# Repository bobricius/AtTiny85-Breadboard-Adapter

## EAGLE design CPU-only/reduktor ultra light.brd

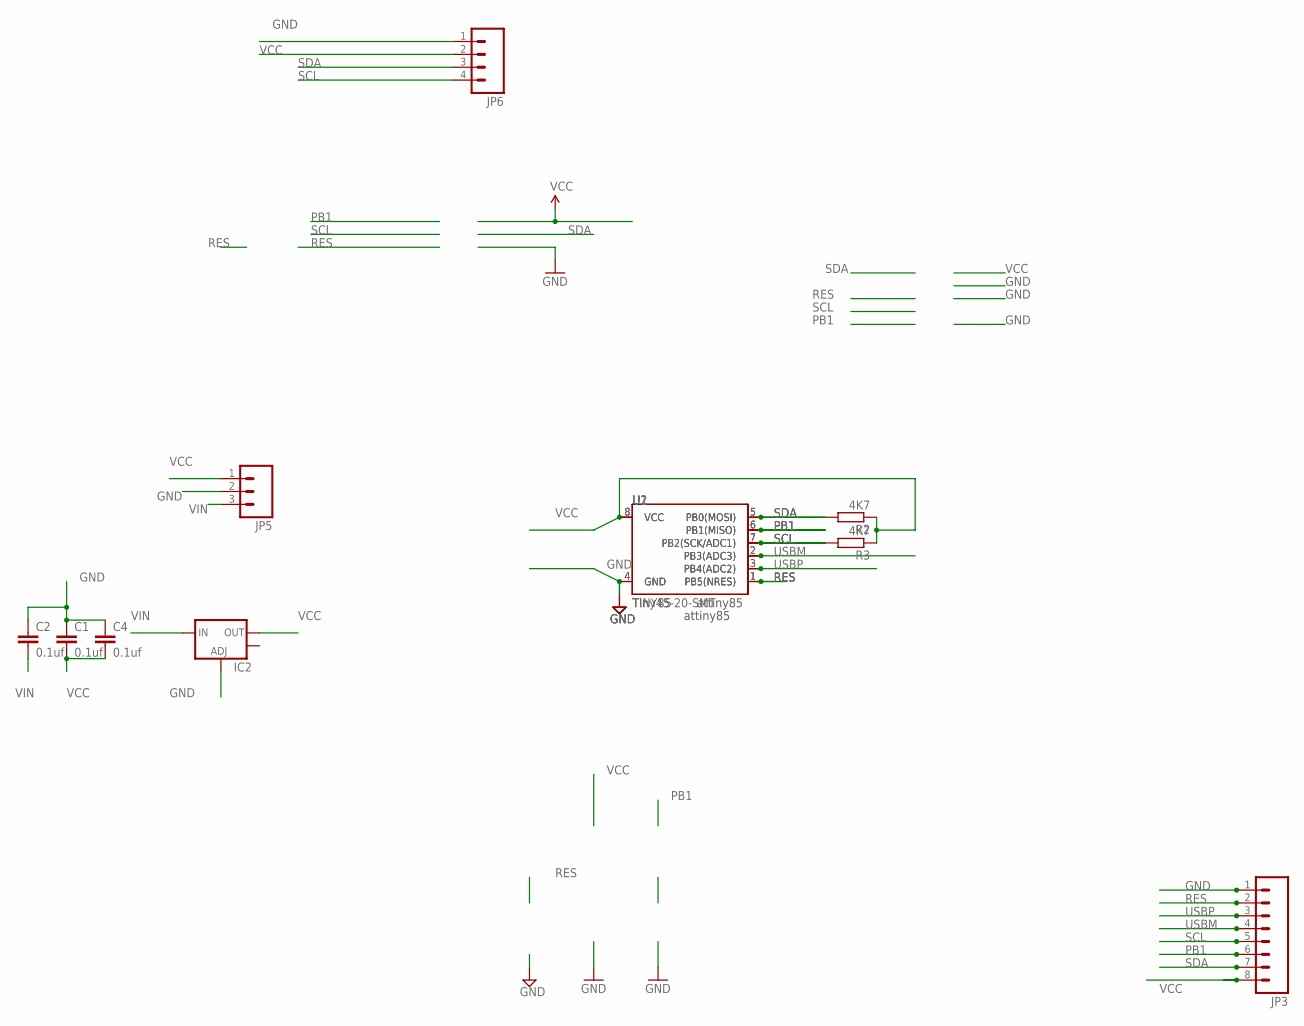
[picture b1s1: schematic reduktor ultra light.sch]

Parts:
C1, C2, C4: 0.1uf; 0603-CAP
IC2: V_REG_LM1117SOT223; SOT223
JP3: M08LOCK; 1X08_LOCK
JP5: M03LOCK; 1X03_LOCK
JP6: M04PTH; 1X04
R2, R3: 4K7; R0603
U1: TINY85; DIP08
U2: Tiny45-20-SMT; SO08-EIAJ

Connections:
GND: C1.1, C2.1, C4.1, IC2.1 (ADJ), JP3.1, JP5.2, JP6.1, U1.4 (GND), U2.4 (GND)
PB1: JP3.6, U1.6 (PB1(MISO)), U2.6 (PB1(MISO))
RES: JP3.2, U1.1 (PB5(NRES)), U2.1 (PB5(NRES))
SCL: JP3.5, JP6.4, R3.2, U1.7 (PB2(SCK/ADC1)), U2.7 (PB2(SCK/ADC1))
SDA: JP3.7, JP6.3, R2.2, U1.5 (PB0(MOSI)), U2.5 (PB0(MOSI))
USBM: JP3.4, U1.2 (PB3(ADC3)), U2.2 (PB3(ADC3))
USBP: JP3.3, U1.3 (PB4(ADC2)), U2.3 (PB4(ADC2))
VCC: C1.2, C4.2, IC2.2 (OUT), JP3.8, JP5.1, JP6.2, R2.1, R3.1, U1.8 (VCC), U2.8 (VCC)
VIN: C2.2, IC2.3 (IN), JP5.3

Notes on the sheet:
attiny85

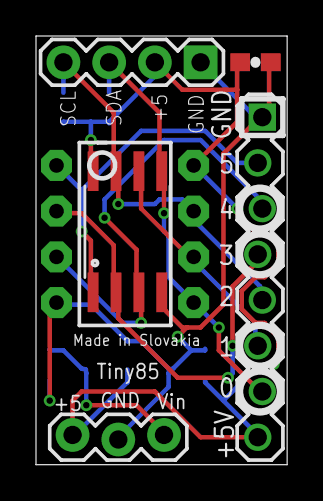
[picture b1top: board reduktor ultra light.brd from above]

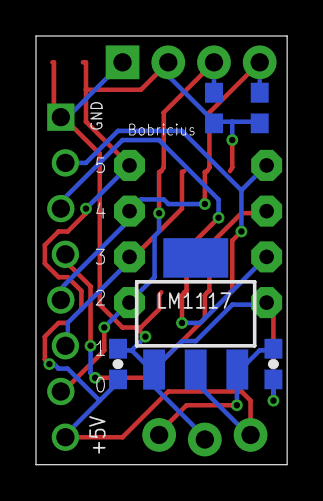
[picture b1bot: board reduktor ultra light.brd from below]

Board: 2 copper layers, 14.0 x 23.8 mm, 11 parts (5 on the bottom side), 9 nets.

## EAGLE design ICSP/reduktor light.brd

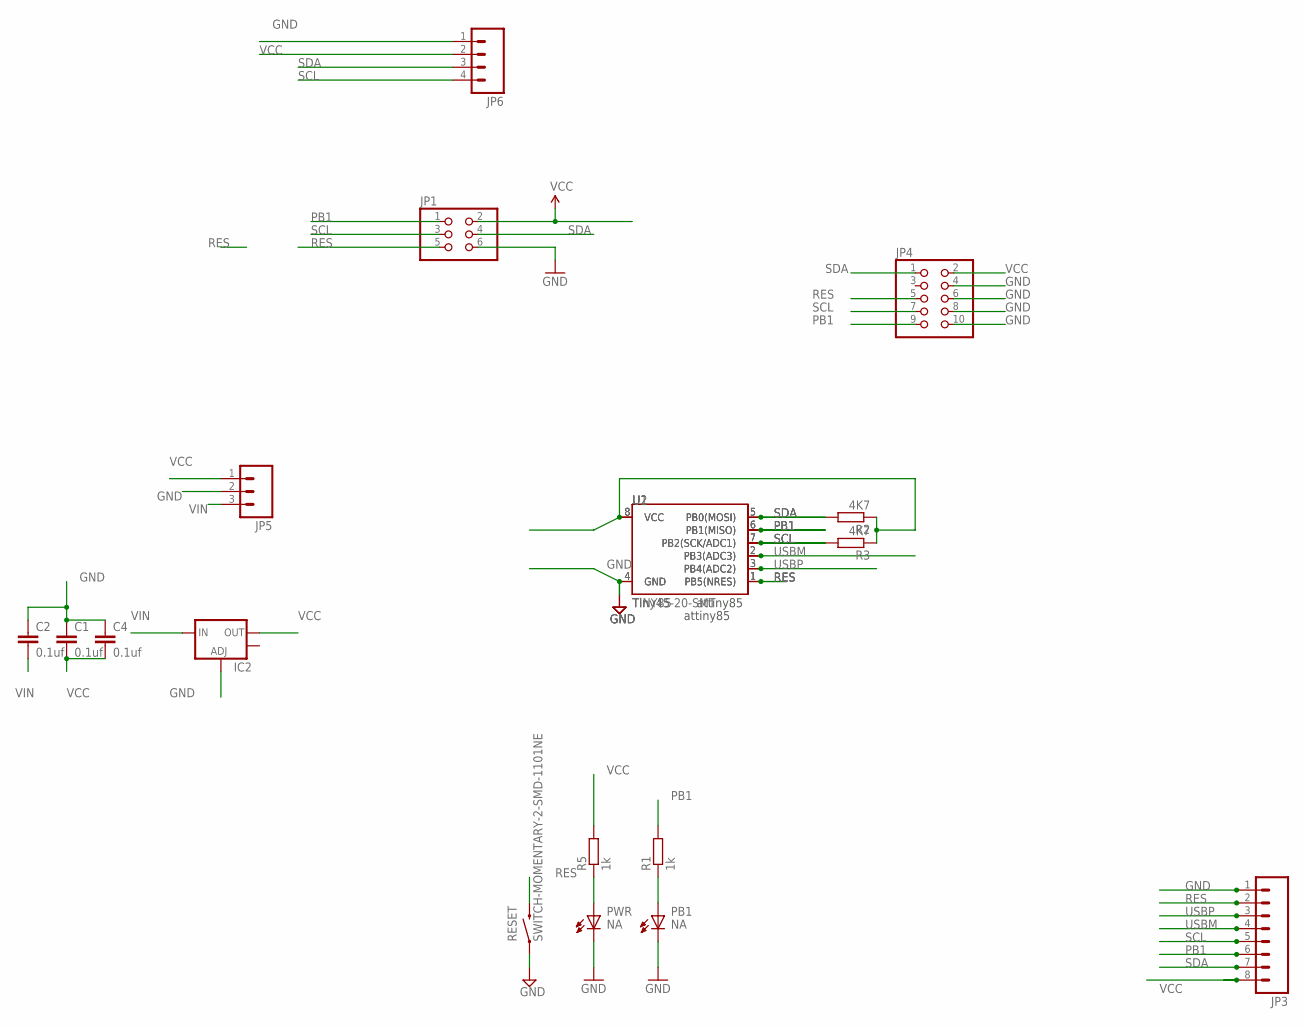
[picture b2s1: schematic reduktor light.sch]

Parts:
C1, C2, C4: 0.1uf; 0603-CAP
IC2: V_REG_LM1117SOT223; SOT223
JP1: PINHD-2X3; 2X03
JP3: M08LOCK_LONGPADS; 1X08_LOCK_LONGPADS
JP4: PINHD-2X5; 2X05
JP5: M03LONGPADS; 1X03_LONGPADS
JP6: M04PTH; 1X04
PB1: NA; LED-0603
PWR: NA; LED-0603
R1, R5: 1k; R0603
R2, R3: 4K7; R0603
RESET: SWITCH-MOMENTARY-2-SMD-1101NE; TACTILE-SWITCH-1101NE
U1: TINY85; DIP08
U2: Tiny45-20-SMT; SO08-EIAJ

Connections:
GND: C1.1, C2.1, C4.1, IC2.1 (ADJ), JP1.6, JP3.1, JP4.4, JP4.6, JP4.8, JP4.10, JP5.2, JP6.1, PB1.C, PWR.C, RESET.P$1 (1), U1.4 (GND), U2.4 (GND)
unnamed: PWR.A, R5.1
PB1: JP1.1, JP3.6, JP4.9, R1.2, U1.6 (PB1(MISO)), U2.6 (PB1(MISO))
PIN1R: PB1.A, R1.1
RES: JP1.5, JP3.2, JP4.5, RESET.P$2 (2), U1.1 (PB5(NRES)), U2.1 (PB5(NRES))
SCL: JP1.3, JP3.5, JP4.7, JP6.4, R3.2, U1.7 (PB2(SCK/ADC1)), U2.7 (PB2(SCK/ADC1))
SDA: JP1.4, JP3.7, JP4.1, JP6.3, R2.2, U1.5 (PB0(MOSI)), U2.5 (PB0(MOSI))
USBM: JP3.4, U1.2 (PB3(ADC3)), U2.2 (PB3(ADC3))
USBP: JP3.3, U1.3 (PB4(ADC2)), U2.3 (PB4(ADC2))
VCC: C1.2, C4.2, IC2.2 (OUT), JP1.2, JP3.8, JP4.2, JP5.1, JP6.2, R2.1, R3.1, R5.2, U1.8 (VCC), U2.8 (VCC)
VIN: C2.2, IC2.3 (IN), JP5.3

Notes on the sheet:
attiny85

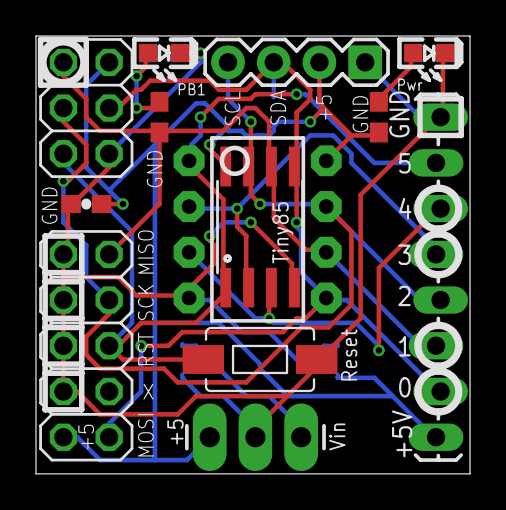
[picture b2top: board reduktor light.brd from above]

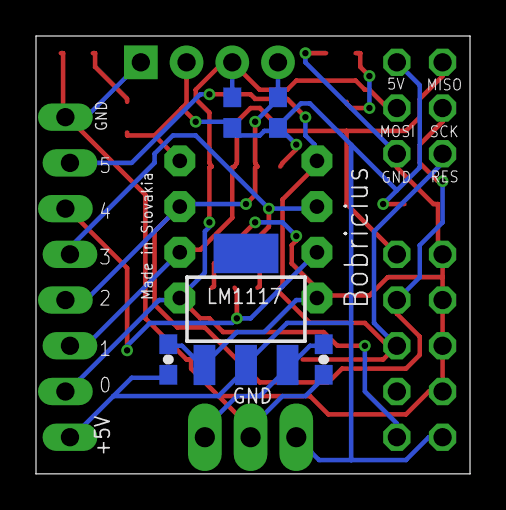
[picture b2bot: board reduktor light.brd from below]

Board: 2 copper layers, 24.1 x 24.3 mm, 18 parts (5 on the bottom side), 11 nets.

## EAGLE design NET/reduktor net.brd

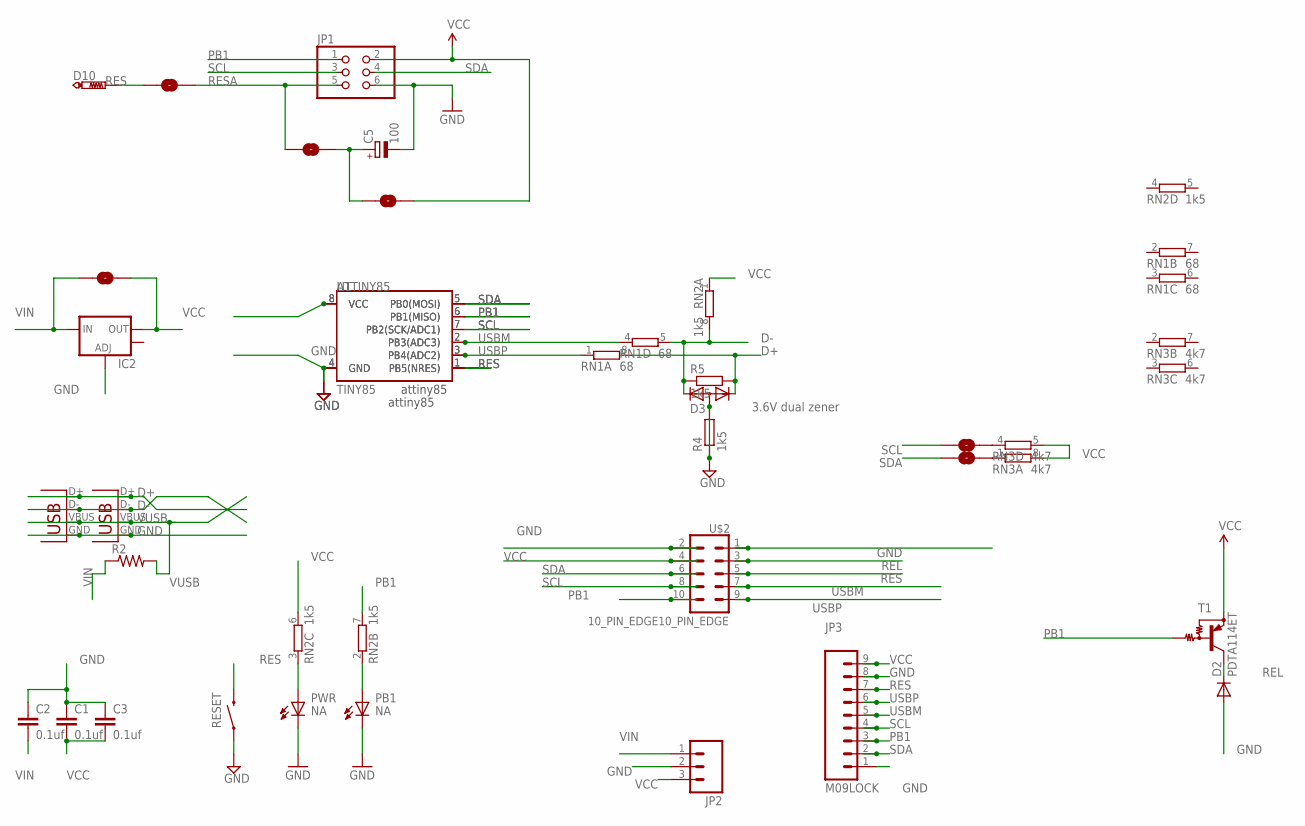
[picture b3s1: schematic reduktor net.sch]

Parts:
ATTINY85: ATTINY45; SO08-EIAJ
C1, C2, C3: 0.1uf; 0603-CAP
C5: 100; 153CLV-0405
D2: DIODESOD; SOD-323
D3: 3.6V dual zener; SOT23
D10: PTR1TP14SQ; TP14SQ
FUSE1, FUSE2, FUSE3, FUSE4, FUSE5, FUSE6: SOLDERJUMPERNO; SJ_2S-NO
IC2: V_REG_LM1117SOT223; SOT223
JP1: PINHD-2X3; 2X03
JP2: M03LOCK; 1X03_LOCK
JP3: M09LOCK; 1X09_LOCK
PB1: NA; LED-0603
PWR: NA; LED-0603
R2: RESISTOR0603-RES; 0603-RES
R4, R5: 1k5; R0603
RESET: SWITCH-MOMENTARY-2-SMD-1101NE; TACTILE-SWITCH-1101NE
RN1: 68; 0603-ARC
RN2: 1k5; 0603-ARC
RN3: 4k7; 0603-ARC
T1: PDTA114ET; ES_SOT23-3
U1: TINY85; DIP08
U$2: 10_PIN_EDGE10_PIN_EDGE; 10_PIN_EDGE
X5: USBSMD; USB-MINIB
X6: USB-MICROB

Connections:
D+: D3.1 (K1), R5.2, RN1.8 (2), X5.D+, X6.D+
D-: D3.2 (K2), R5.1, RN1.5 (2), RN2.8 (2), X5.D-, X6.D-
GND: ATTINY85.4 (GND), C1.1, C2.1, C3.1, C5.-, D2.2 (A), D3.3 (A), IC2.1 (ADJ), JP1.6, JP2.2, JP3.1, JP3.8, PB1.C, PWR.C, R4.1, R4.2, RESET.P$1 (1), U1.4 (GND), U$2.1, U$2.2, X5.GND, X6.GND
unnamed: PWR.A, RN2.3 (1)
unnamed: FUSE4.2, RN3.4 (1)
unnamed: FUSE5.2, RN3.1
unnamed: C5.+, FUSE3.2, FUSE6.2
PB1: ATTINY85.6 (PB1(MISO)), JP1.1, JP3.3, RN2.7 (2), T1.1 (B), U1.6 (PB1(MISO)), U$2.10
PIN1R: PB1.A, RN2.2 (1)
REL: D2.1 (C), T1.3 (C), U$2.3
RES: ATTINY85.1 (PB5(NRES)), D10.TP, FUSE1.1, JP3.7, RESET.P$2 (2), U1.1 (PB5(NRES)), U$2.5
RESA: FUSE1.2, FUSE3.1, JP1.5
SCL: ATTINY85.7 (PB2(SCK/ADC1)), FUSE4.1, JP1.3, JP3.4, U1.7 (PB2(SCK/ADC1)), U$2.8
SDA: ATTINY85.5 (PB0(MOSI)), FUSE5.1, JP1.4, JP3.2, U1.5 (PB0(MOSI)), U$2.6
USBM: ATTINY85.2 (PB3(ADC3)), JP3.5, RN1.4 (1), U1.2 (PB3(ADC3)), U$2.7
USBP: ATTINY85.3 (PB4(ADC2)), JP3.6, RN1.1, U1.3 (PB4(ADC2)), U$2.9
VCC: ATTINY85.8 (VCC), C1.2, C3.2, FUSE2.2, FUSE6.1, IC2.2 (OUT), JP1.2, JP2.3, JP3.9, RN2.1, RN2.6 (2), RN3.5 (2), RN3.8 (2), T1.2 (E), U1.8 (VCC), U$2.4
VIN: C2.2, FUSE2.1, IC2.3 (IN), JP2.1, R2.1
VUSB: R2.2, X5.VBUS, X6.VBUS

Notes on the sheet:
attiny85

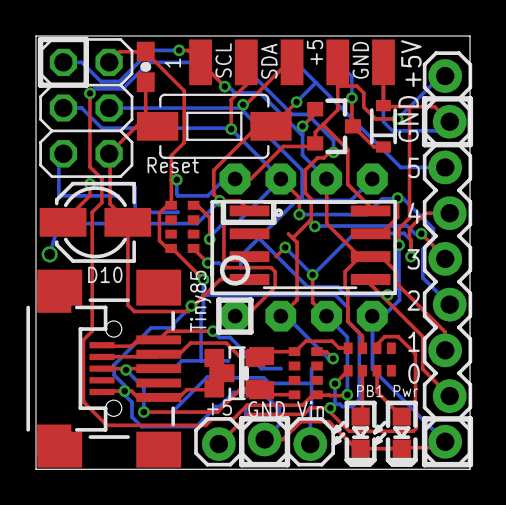
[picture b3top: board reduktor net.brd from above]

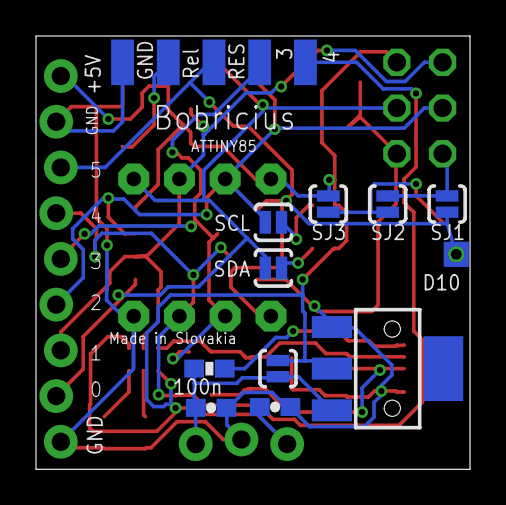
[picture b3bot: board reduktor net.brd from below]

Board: 2 copper layers, 24.1 x 24.1 mm, 32 parts (12 on the bottom side), 19 nets.

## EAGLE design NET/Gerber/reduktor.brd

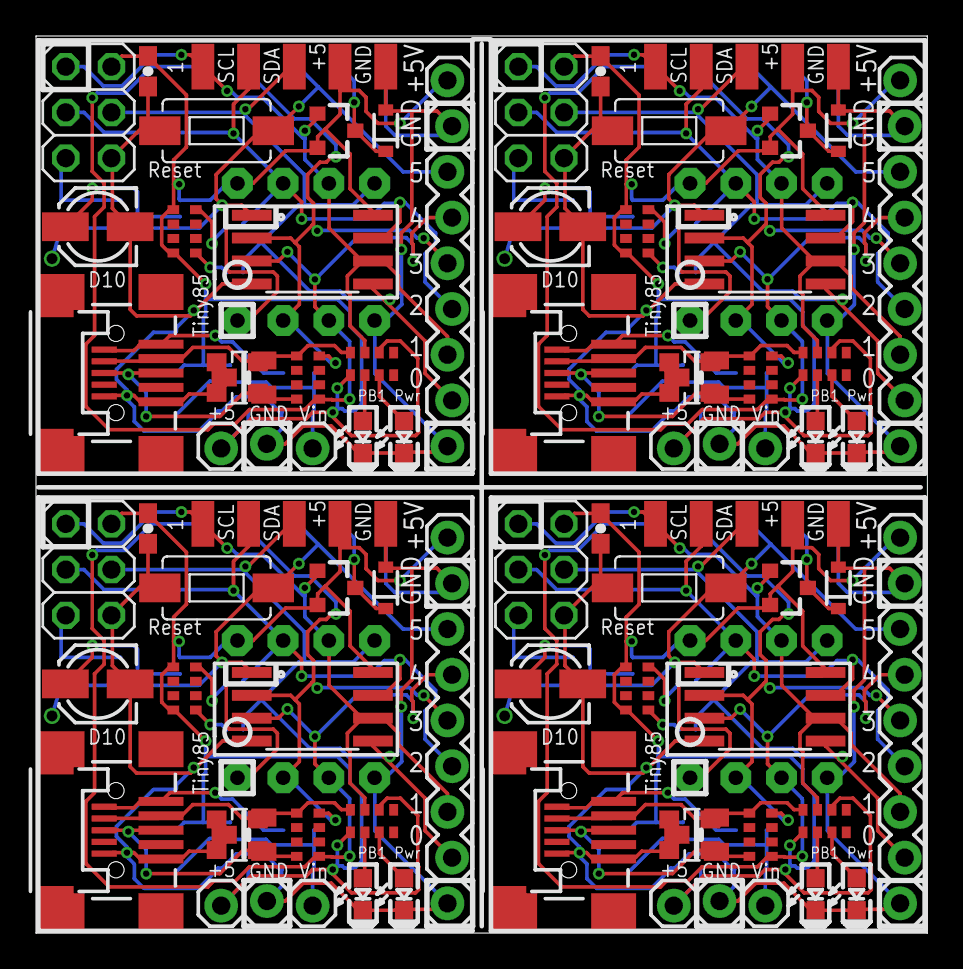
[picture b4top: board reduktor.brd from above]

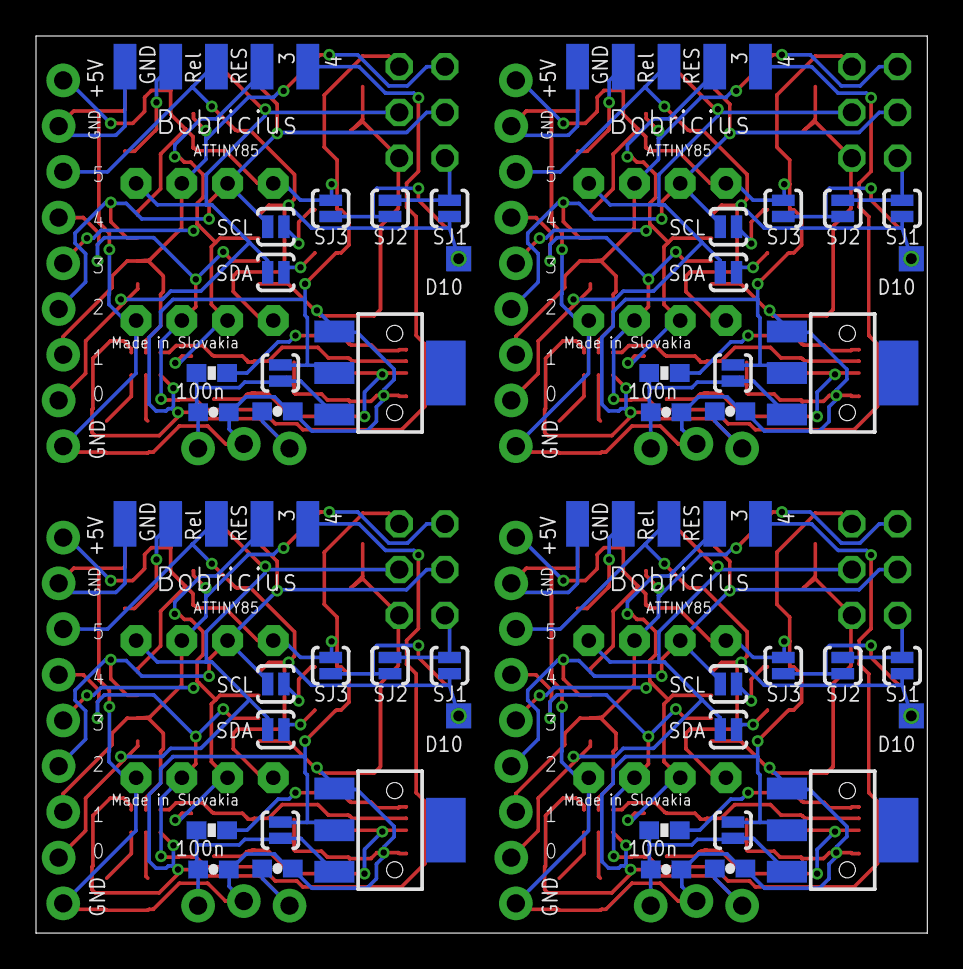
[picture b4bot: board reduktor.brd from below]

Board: 2 copper layers, 49.5 x 49.8 mm, 128 parts (48 on the bottom side), 76 nets.

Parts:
ATTINY1, ATTINY2, ATTINY3, ATTINY85: ATTINY45; SO08-EIAJ
C1, C2, C3, C4, C6, C7, C9, C10, C11, C13, C14, C15: 0.1uf; 0603-CAP
C5, C8, C12, C16: 100; 153CLV-0405
D1, D2, D6, D9: SOD-323
D3, D4, D7, D11: 3.6V dual zener; SOT23
D5, D8, D10, D12: PTR1TP14SQ; TP14SQ
FUSE1, FUSE2, FUSE3, FUSE4, FUSE5, FUSE6, FUSE7, FUSE8, FUSE9, FUSE10, FUSE11, FUSE12, FUSE13, FUSE14, FUSE15, FUSE16, FUSE17, FUSE18, FUSE19, FUSE20, FUSE21, FUSE22, FUSE23, FUSE24: SOLDERJUMPERNO; SJ_2S-NO
IC1, IC2, IC3, IC4: SOT223
JP1, JP6, JP9, JP12: 2X03
JP2, JP4, JP7, JP10: 1X03_LOCK
JP3, JP5, JP8, JP11: M09LOCK; 1X09_LOCK
PB1, PB2, PB3, PB4: NA; LED-0603
PWR, PWR1, PWR2, PWR3: NA; LED-0603
R1, R2, R7, R10: 0603-RES
R3, R4, R5, R6, R8, R9, R11, R12: 1k5; R0603
RESET, RESET1, RESET2, RESET3: TACTILE-SWITCH-1101NE
RN1, RN4, RN7, RN10: 68; 0603-ARC
RN2, RN5, RN8, RN11: 1k5; 0603-ARC
RN3, RN6, RN9, RN12: 4k7; 0603-ARC
T1, T2, T3, T4: PDTA114ET; ES_SOT23-3
U1, U2, U3, U4: TINY85; DIP08
U$1, U$2, U$3, U$4: 10_PIN_EDGE10_PIN_EDGE; 10_PIN_EDGE
X1, X3, X5, X7: USBSMD; USB-MINIB
X2, X4, X6, X8: USB-MICROB

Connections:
D+: D3.1, R5.2, RN1.8, X5.D+, X6.D+
D+1: D4.1, R6.2, RN4.8, X1.D+, X2.D+
D+2: D7.1, R9.2, RN7.8, X3.D+, X4.D+
D+3: D11.1, R12.2, RN10.8, X7.D+, X8.D+
D-: D3.2, R5.1, RN1.5, RN2.8, X5.D-, X6.D-
D-1: D4.2, R6.1, RN4.5, RN5.8, X1.D-, X2.D-
D-2: D7.2, R9.1, RN7.5, RN8.8, X3.D-, X4.D-
D-3: D11.2, R12.1, RN10.5, RN11.8, X7.D-, X8.D-
GND: ATTINY85.4, C1.1, C2.1, C3.1, C5.-, D2.2, D3.3, IC2.1, JP1.6, JP2.2, JP3.1, JP3.8, PB1.C, PWR.C, R4.1, R4.2, RESET.P$1, U1.4, U$2.1, U$2.2, X5.GND, X6.GND
GND1: ATTINY1.4, C4.1, C6.1, C7.1, C8.-, D1.2, D4.3, IC1.1, JP4.2, JP5.1, JP5.8, JP6.6, PB2.C, PWR1.C, R3.1, R3.2, RESET1.P$1, U2.4, U$1.1, U$1.2, X1.GND, X2.GND
GND2: ATTINY2.4, C9.1, C10.1, C11.1, C12.-, D6.2, D7.3, IC3.1, JP7.2, JP8.1, JP8.8, JP9.6, PB3.C, PWR2.C, R8.1, R8.2, RESET2.P$1, U3.4, U$3.1, U$3.2, X3.GND, X4.GND
GND3: ATTINY3.4, C13.1, C14.1, C15.1, C16.-, D9.2, D11.3, IC4.1, JP10.2, JP11.1, JP11.8, JP12.6, PB4.C, PWR3.C, R11.1, R11.2, RESET3.P$1, U4.4, U$4.1, U$4.2, X7.GND, X8.GND
unnamed: PWR1.A, RN5.3
unnamed: FUSE10.2, RN6.4
unnamed: PWR.A, RN2.3
unnamed: FUSE11.2, RN6.1
unnamed: C8.+, FUSE9.2, FUSE12.2
unnamed: PWR2.A, RN8.3
unnamed: FUSE16.2, RN9.4
unnamed: FUSE4.2, RN3.4
unnamed: FUSE5.2, RN3.1
unnamed: C5.+, FUSE3.2, FUSE6.2
unnamed: FUSE17.2, RN9.1
unnamed: C12.+, FUSE15.2, FUSE18.2
unnamed: PWR3.A, RN11.3
unnamed: FUSE22.2, RN12.4
unnamed: FUSE23.2, RN12.1
unnamed: C16.+, FUSE21.2, FUSE24.2
PB1: ATTINY85.6, JP1.1, JP3.3, RN2.7, T1.1, U1.6, U$2.10
PB2: ATTINY1.6, JP5.3, JP6.1, RN5.7, T2.1, U2.6, U$1.10
PB3: ATTINY2.6, JP8.3, JP9.1, RN8.7, T3.1, U3.6, U$3.10
PB4: ATTINY3.6, JP11.3, JP12.1, RN11.7, T4.1, U4.6, U$4.10
PIN1R: PB1.A, RN2.2
PIN1R1: PB2.A, RN5.2
PIN1R2: PB3.A, RN8.2
PIN1R3: PB4.A, RN11.2
REL: D2.1, T1.3, U$2.3
REL1: D1.1, T2.3, U$1.3
REL2: D6.1, T3.3, U$3.3
REL3: D9.1, T4.3, U$4.3
RES: ATTINY85.1, D10.TP, FUSE1.1, JP3.7, RESET.P$2, U1.1, U$2.5
RES1: ATTINY1.1, D5.TP, FUSE8.1, JP5.7, RESET1.P$2, U2.1, U$1.5
RES2: ATTINY2.1, D8.TP, FUSE14.1, JP8.7, RESET2.P$2, U3.1, U$3.5
RES3: ATTINY3.1, D12.TP, FUSE20.1, JP11.7, RESET3.P$2, U4.1, U$4.5
RESA: FUSE1.2, FUSE3.1, JP1.5
RESA1: FUSE8.2, FUSE9.1, JP6.5
RESA2: FUSE14.2, FUSE15.1, JP9.5
RESA3: FUSE20.2, FUSE21.1, JP12.5
SCL: ATTINY85.7, FUSE4.1, JP1.3, JP3.4, U1.7, U$2.8
SCL1: ATTINY1.7, FUSE10.1, JP5.4, JP6.3, U2.7, U$1.8
SCL2: ATTINY2.7, FUSE16.1, JP8.4, JP9.3, U3.7, U$3.8
SCL3: ATTINY3.7, FUSE22.1, JP11.4, JP12.3, U4.7, U$4.8
SDA: ATTINY85.5, FUSE5.1, JP1.4, JP3.2, U1.5, U$2.6
SDA1: ATTINY1.5, FUSE11.1, JP5.2, JP6.4, U2.5, U$1.6
SDA2: ATTINY2.5, FUSE17.1, JP8.2, JP9.4, U3.5, U$3.6
SDA3: ATTINY3.5, FUSE23.1, JP11.2, JP12.4, U4.5, U$4.6
USBM: ATTINY85.2, JP3.5, RN1.4, U1.2, U$2.7
USBM1: ATTINY1.2, JP5.5, RN4.4, U2.2, U$1.7
USBM2: ATTINY2.2, JP8.5, RN7.4, U3.2, U$3.7
USBM3: ATTINY3.2, JP11.5, RN10.4, U4.2, U$4.7
USBP: ATTINY85.3, JP3.6, RN1.1, U1.3, U$2.9
USBP1: ATTINY1.3, JP5.6, RN4.1, U2.3, U$1.9
USBP2: ATTINY2.3, JP8.6, RN7.1, U3.3, U$3.9
USBP3: ATTINY3.3, JP11.6, RN10.1, U4.3, U$4.9
VCC: ATTINY85.8, C1.2, C3.2, FUSE2.2, FUSE6.1, IC2.2, JP1.2, JP2.3, JP3.9, RN2.1, RN2.6, RN3.5, RN3.8, T1.2, U1.8, U$2.4
VCC1: ATTINY1.8, C4.2, C7.2, FUSE7.2, FUSE12.1, IC1.2, JP4.3, JP5.9, JP6.2, RN5.1, RN5.6, RN6.5, RN6.8, T2.2, U2.8, U$1.4
VCC2: ATTINY2.8, C9.2, C11.2, FUSE13.2, FUSE18.1, IC3.2, JP7.3, JP8.9, JP9.2, RN8.1, RN8.6, RN9.5, RN9.8, T3.2, U3.8, U$3.4
VCC3: ATTINY3.8, C13.2, C15.2, FUSE19.2, FUSE24.1, IC4.2, JP10.3, JP11.9, JP12.2, RN11.1, RN11.6, RN12.5, RN12.8, T4.2, U4.8, U$4.4
VIN: C2.2, FUSE2.1, IC2.3, JP2.1, R2.1
VIN1: C6.2, FUSE7.1, IC1.3, JP4.1, R1.1
VIN2: C10.2, FUSE13.1, IC3.3, JP7.1, R7.1
VIN3: C14.2, FUSE19.1, IC4.3, JP10.1, R10.1
VUSB: R2.2, X5.VBUS, X6.VBUS
VUSB1: R1.2, X1.VBUS, X2.VBUS
VUSB2: R7.2, X3.VBUS, X4.VBUS
VUSB3: R10.2, X7.VBUS, X8.VBUS

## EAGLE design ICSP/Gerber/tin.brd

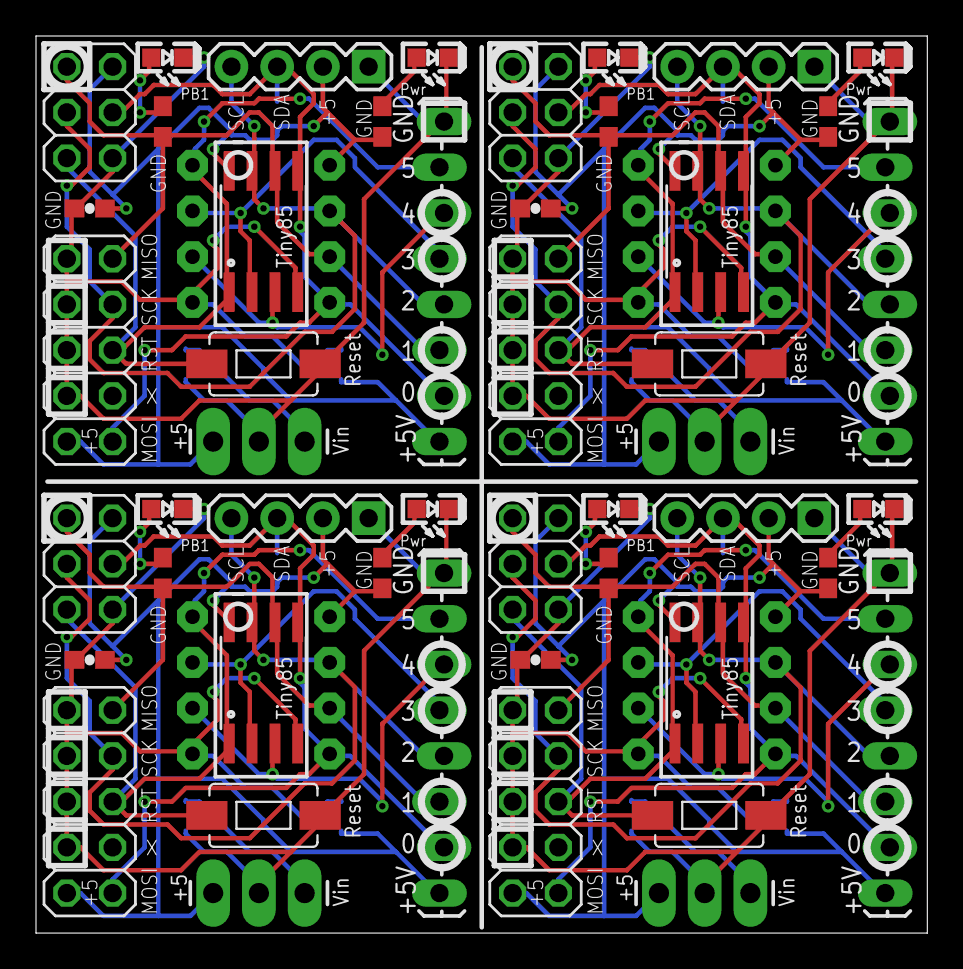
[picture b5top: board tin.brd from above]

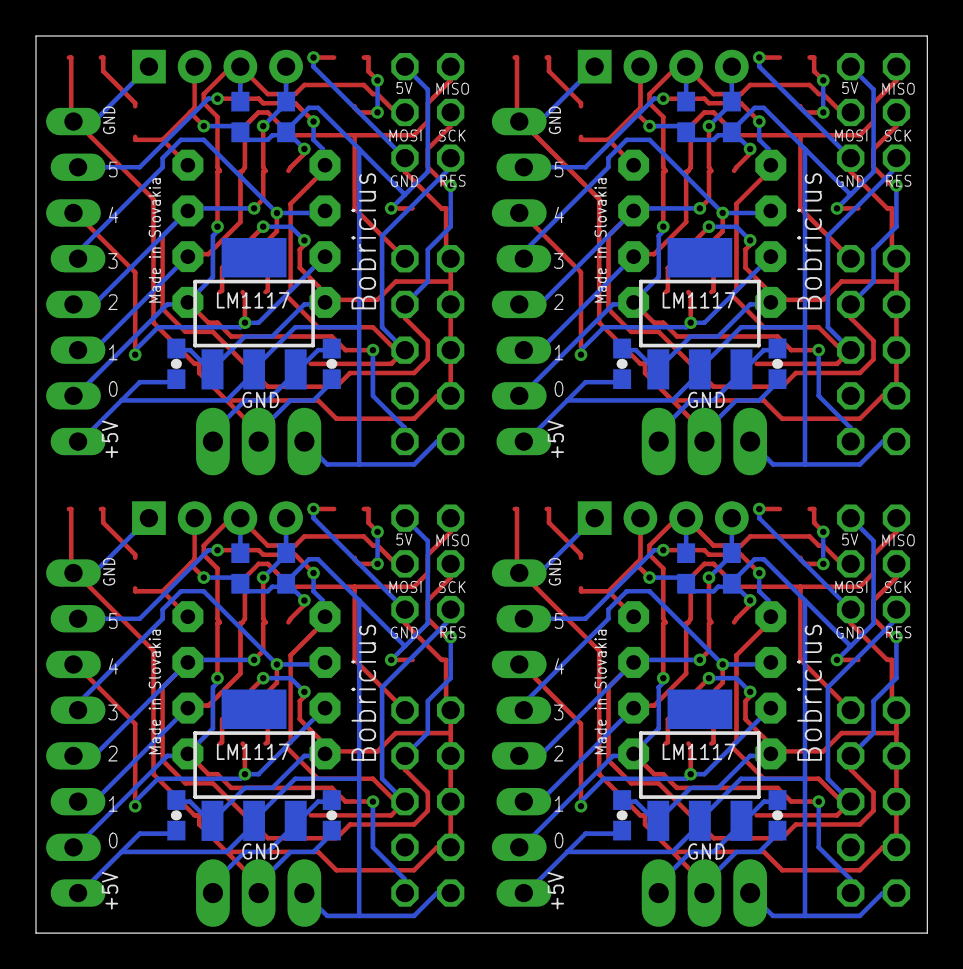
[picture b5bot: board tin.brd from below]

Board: 2 copper layers, 49.5 x 49.8 mm, 72 parts (20 on the bottom side), 44 nets.

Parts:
C1, C2, C3, C4, C5, C6, C7, C8, C9, C10, C11, C12: 0.1uf; 0603-CAP
IC1, IC2, IC3, IC4: SOT223
JP1, JP8, JP13, JP18: 2X03
JP2, JP4, JP11, JP16: 2X05
JP3, JP10, JP15, JP20: 1X08_LOCK_LONGPADS
JP5, JP7, JP12, JP17: 1X03_LONGPADS
JP6, JP9, JP14, JP19: 1X04
PB1, PB2, PB3, PB4: NA; LED-0603
PWR, PWR1, PWR2, PWR3: NA; LED-0603
R1, R4, R5, R6, R9, R10, R13, R14: 1k; R0603
R2, R3, R7, R8, R11, R12, R15, R16: 4K7; R0603
RESET, RESET1, RESET2, RESET3: SWITCH-MOMENTARY-2-SMD-1101NE; TACTILE-SWITCH-1101NE
U1, U3, U5, U7: TINY85; DIP08
U2, U4, U6, U8: Tiny45-20-SMT; SO08-EIAJ

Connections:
GND: C1.1, C2.1, C4.1, IC2.1, JP1.6, JP3.1, JP4.4, JP4.6, JP4.8, JP4.10, JP5.2, JP6.1, PB1.C, PWR.C, RESET.P$1, U1.4, U2.4
GND1: C3.1, C5.1, C6.1, IC1.1, JP2.4, JP2.6, JP2.8, JP2.10, JP7.2, JP8.6, JP9.1, JP10.1, PB2.C, PWR1.C, RESET1.P$1, U3.4, U4.4
GND2: C7.1, C8.1, C9.1, IC3.1, JP11.4, JP11.6, JP11.8, JP11.10, JP12.2, JP13.6, JP14.1, JP15.1, PB3.C, PWR2.C, RESET2.P$1, U5.4, U6.4
GND3: C10.1, C11.1, C12.1, IC4.1, JP16.4, JP16.6, JP16.8, JP16.10, JP17.2, JP18.6, JP19.1, JP20.1, PB4.C, PWR3.C, RESET3.P$1, U7.4, U8.4
unnamed: PWR1.A, R4.1
unnamed: PWR2.A, R9.1
unnamed: PWR.A, R5.1
unnamed: PWR3.A, R13.1
PB1: JP1.1, JP3.6, JP4.9, R1.2, U1.6, U2.6
PB2: JP2.9, JP8.1, JP10.6, R6.2, U3.6, U4.6
PB3: JP11.9, JP13.1, JP15.6, R10.2, U5.6, U6.6
PB4: JP16.9, JP18.1, JP20.6, R14.2, U7.6, U8.6
PIN1R: PB1.A, R1.1
PIN1R1: PB2.A, R6.1
PIN1R2: PB3.A, R10.1
PIN1R3: PB4.A, R14.1
RES: JP1.5, JP3.2, JP4.5, RESET.P$2, U1.1, U2.1
RES1: JP2.5, JP8.5, JP10.2, RESET1.P$2, U3.1, U4.1
RES2: JP11.5, JP13.5, JP15.2, RESET2.P$2, U5.1, U6.1
RES3: JP16.5, JP18.5, JP20.2, RESET3.P$2, U7.1, U8.1
SCL: JP1.3, JP3.5, JP4.7, JP6.4, R3.2, U1.7, U2.7
SCL1: JP2.7, JP8.3, JP9.4, JP10.5, R8.2, U3.7, U4.7
SCL2: JP11.7, JP13.3, JP14.4, JP15.5, R12.2, U5.7, U6.7
SCL3: JP16.7, JP18.3, JP19.4, JP20.5, R16.2, U7.7, U8.7
SDA: JP1.4, JP3.7, JP4.1, JP6.3, R2.2, U1.5, U2.5
SDA1: JP2.1, JP8.4, JP9.3, JP10.7, R7.2, U3.5, U4.5
SDA2: JP11.1, JP13.4, JP14.3, JP15.7, R11.2, U5.5, U6.5
SDA3: JP16.1, JP18.4, JP19.3, JP20.7, R15.2, U7.5, U8.5
USBM: JP3.4, U1.2, U2.2
USBM1: JP10.4, U3.2, U4.2
USBM2: JP15.4, U5.2, U6.2
USBM3: JP20.4, U7.2, U8.2
USBP: JP3.3, U1.3, U2.3
USBP1: JP10.3, U3.3, U4.3
USBP2: JP15.3, U5.3, U6.3
USBP3: JP20.3, U7.3, U8.3
VCC: C1.2, C4.2, IC2.2, JP1.2, JP3.8, JP4.2, JP5.1, JP6.2, R2.1, R3.1, R5.2, U1.8, U2.8
VCC1: C3.2, C6.2, IC1.2, JP2.2, JP7.1, JP8.2, JP9.2, JP10.8, R4.2, R7.1, R8.1, U3.8, U4.8
VCC2: C7.2, C9.2, IC3.2, JP11.2, JP12.1, JP13.2, JP14.2, JP15.8, R9.2, R11.1, R12.1, U5.8, U6.8
VCC3: C10.2, C12.2, IC4.2, JP16.2, JP17.1, JP18.2, JP19.2, JP20.8, R13.2, R15.1, R16.1, U7.8, U8.8
VIN: C2.2, IC2.3, JP5.3
VIN1: C5.2, IC1.3, JP7.3
VIN2: C8.2, IC3.3, JP12.3
VIN3: C11.2, IC4.3, JP17.3

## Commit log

2014-12-17 :circus_tent: Added .gitattributes & .gitignore files
2014-12-17 first upload

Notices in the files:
parts and their libraries:
SparkFun: Licensing: CC v3.0 Share-Alike You are welcome to use this library for commercial purposes.
